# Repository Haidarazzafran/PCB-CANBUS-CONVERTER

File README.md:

# PCB-CANBUS-CONVERTER
Schematic and PCB KiCAD

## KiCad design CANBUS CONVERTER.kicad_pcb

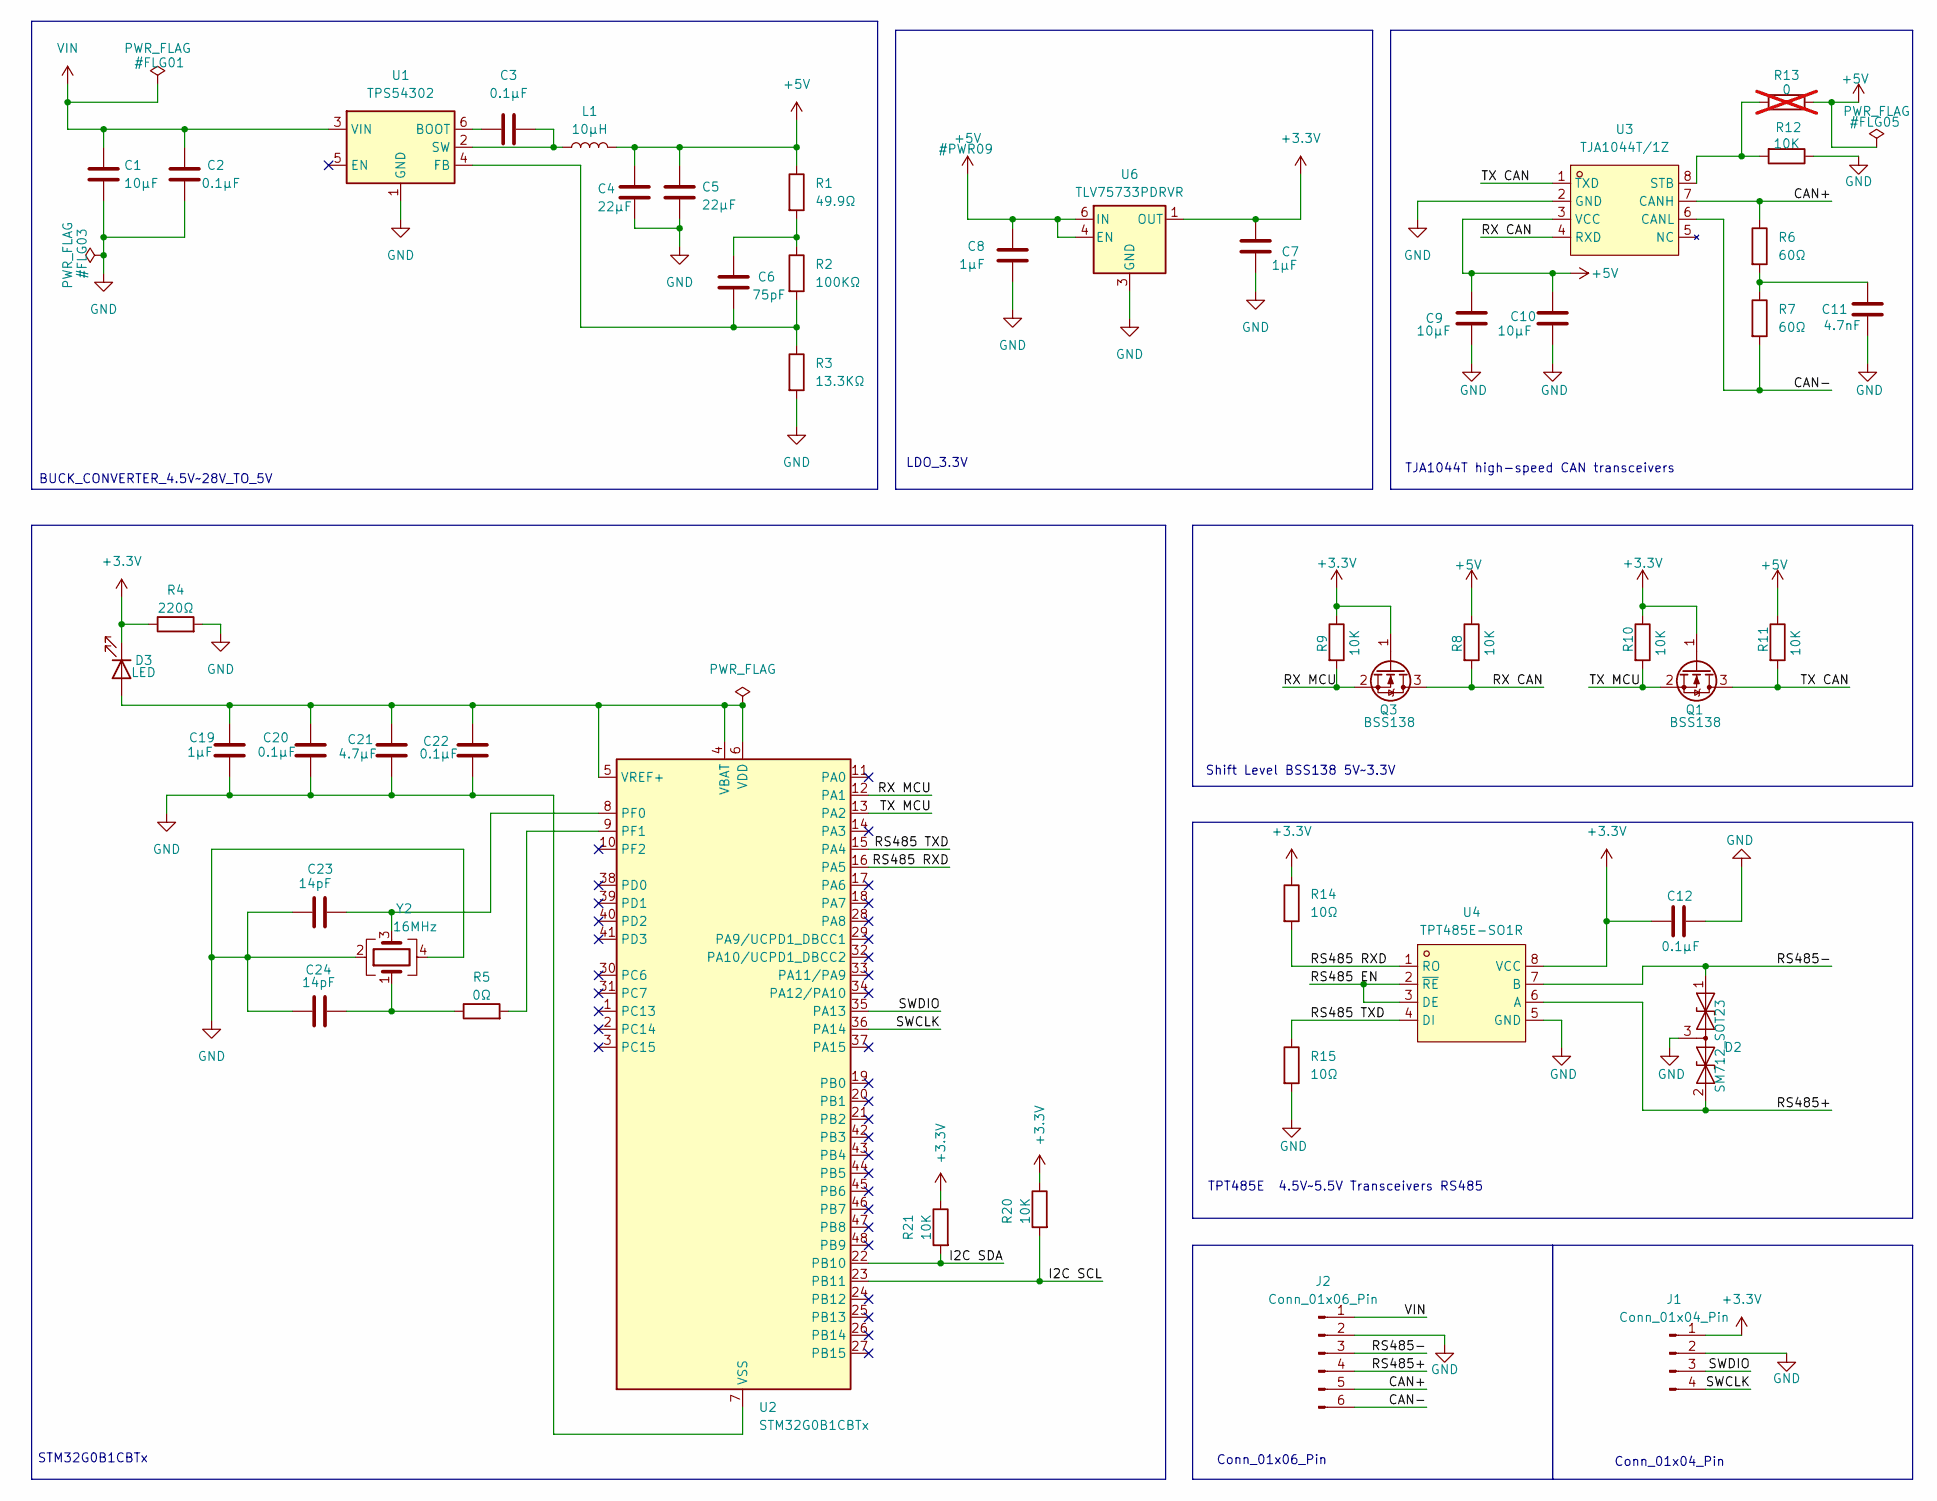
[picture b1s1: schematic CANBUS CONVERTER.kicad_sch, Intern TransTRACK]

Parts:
C1, C9, C10: 10µF; C_0805_2012Metric_Pad1.18x1.45mm_HandSolder
C2, C3, C12, C20, C22: 0.1µF; C_0805_2012Metric_Pad1.18x1.45mm_HandSolder
C4, C5: 22µF; C_0805_2012Metric_Pad1.18x1.45mm_HandSolder
C6: 75pF; C_0805_2012Metric_Pad1.18x1.45mm_HandSolder
C7, C8, C19: 1µF; C_0805_2012Metric_Pad1.18x1.45mm_HandSolder
C11: 4.7nF; C_0805_2012Metric_Pad1.18x1.45mm_HandSolder
C21: 4.7µF; C_0805_2012Metric_Pad1.18x1.45mm_HandSolder
C23, C24: 14pF; C_0805_2012Metric_Pad1.18x1.45mm_HandSolder
D2: SM712_SOT23; SOT-23
D3: LED; LED_0805_2012Metric_Pad1.15x1.40mm_HandSolder
J1: Conn_01x04_Pin; PinSocket_1x04_P2.54mm_Vertical
J2: Conn_01x06_Pin; PinSocket_1x06_P2.54mm_Vertical
L1: 10µH; L_Abracon_ASPI-0630LR
Q1, Q3: BSS138; SOT-23
R1: 49.9Ω; R_0805_2012Metric_Pad1.20x1.40mm_HandSolder
R2: 100KΩ; R_0805_2012Metric_Pad1.20x1.40mm_HandSolder
R3: 13.3KΩ; R_0805_2012Metric_Pad1.20x1.40mm_HandSolder
R4: 220Ω; R_0805_2012Metric_Pad1.20x1.40mm_HandSolder
R5: 0Ω; R_0805_2012Metric_Pad1.20x1.40mm_HandSolder
R6, R7: 60Ω; R_0805_2012Metric_Pad1.20x1.40mm_HandSolder
R8, R9, R10, R11, R12, R20, R21: 10K; R_0805_2012Metric_Pad1.20x1.40mm_HandSolder
R13: 0; R_0805_2012Metric_Pad1.20x1.40mm_HandSolder; not fitted
R14, R15: 10Ω; R_0805_2012Metric_Pad1.20x1.40mm_HandSolder
U1: TPS54302; SOT-23-6
U2: STM32G0B1CBTx; LQFP-48_7x7mm_P0.5mm
U3: TJA1044T/1Z; SOIC-8_L4.9-W3.9-P1.27-LS6.0-BL; LCSC Part C520388
U4: TPT485E-SO1R; SOP-8_L4.9-W3.9-P1.27-LS6.0-BL; LCSC Part C2981238
U6: TLV75733PDRVR; WSON-6-1EP_2x2mm_P0.65mm_EP1x1.6mm
Y2: 16MHz; Crystal_SMD_3225-4Pin_3.2x2.5mm_HandSoldering

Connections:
+3.3V: C7.2, C12.2, D3.1 (K), J1.1, Q1.1 (G), Q3.1 (G), R4.1, R9.1, R10.1, R14.1, R20.1, R21.1, U4.8 (VCC), U6.1 (OUT)
+5V: C4.1, C5.1, C8.1, C9.1, C10.1, L1.2, R1.1, R8.1, R11.1, R13.1, U3.3 (VCC), U6.4 (EN), U6.6 (IN)
/ RS485 EN: U4.2 (~RE), U4.3 (DE)
/CAN+: J2.5, R6.1, U3.7 (CANH)
/CAN-: J2.6, R7.2, U3.6 (CANL)
/I2C SCL: R20.2, U2.23 (PB11)
/I2C SDA: R21.2, U2.22 (PB10)
/RS485 RXD: R14.2, U2.16 (PA5), U4.1 (RO)
/RS485 TXD: R15.1, U2.15 (PA4), U4.4 (DI)
/RS485+: D2.2 (A2), J2.4, U4.6 (A)
/RS485-: D2.1 (A1), J2.3, U4.7 (B)
/RX CAN: Q3.3 (D), R8.2, U3.4 (RXD)
/RX MCU: Q3.2 (S), R9.2, U2.12 (PA1)
/SWCLK: J1.4, U2.36 (PA14)
/SWDIO: J1.3, U2.35 (PA13)
/TX CAN: Q1.3 (D), R11.2, U3.1 (TXD)
/TX MCU: Q1.2 (S), R10.2, U2.13 (PA2)
GND: C1.2, C2.2, C4.2, C5.2, C7.1, C8.2, C9.2, C10.2, C11.2, C12.1, C19.2, C20.2, C21.2, C22.2, C23.1, C24.1, D2.3 (common), J1.2, J2.2, R3.2, R4.2, R12.1, R15.2, U1.1 (GND), U2.7 (VSS), U3.2 (GND), U4.5 (GND), U6.3 (GND), U6.7 (GND), Y2.2, Y2.4
unnamed: C6.1, R1.2, R2.1
unnamed: C11.1, R6.2, R7.1
unnamed: C24.2, R5.1, Y2.1
unnamed: C19.1, C20.1, C21.1, C22.1, D3.2 (A), U2.4 (VBAT), U2.5 (VREF+), U2.6 (VDD)
unnamed: C3.1, U1.6 (BOOT)
unnamed: C6.2, R2.2, R3.1, U1.4 (FB)
unnamed: C3.2, L1.1, U1.2 (SW)
unnamed: C23.2, U2.8 (PF0), Y2.3
unnamed: R5.2, U2.9 (PF1)
unnamed: R12.2, R13.2, U3.8 (STB)
VIN: C1.1, C2.1, J2.1, U1.3 (VIN)

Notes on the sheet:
STM32G0B1CBTx
TPT485E 4.5V~5.5V Transceivers RS485
TJA1044T high-speed CAN transceivers
Shift Level BSS138 5V~3.3V
Conn_01x04_Pin
Conn_01x06_Pin
BUCK_CONVERTER_4.5V~28V_TO_5V
LDO_3.3V

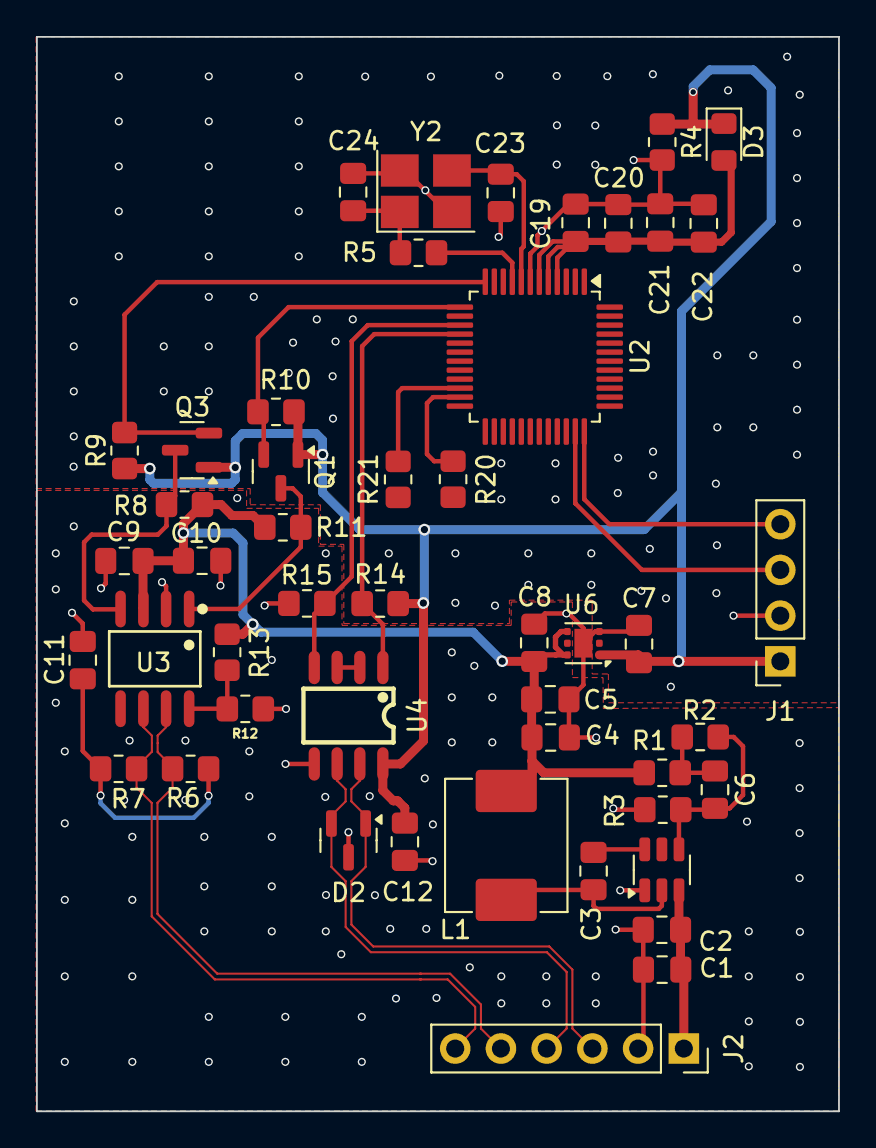
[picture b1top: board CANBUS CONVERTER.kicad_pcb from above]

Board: 4 copper layers, 44.6 x 59.7 mm, 48 parts (0 on the bottom side), 29 nets.

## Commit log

2025-03-04 PCB CAN CONVERTER
2025-03-07 Delete PCB.zip
    delete zip
2025-03-07 schematic PCB
    schematic PCB
